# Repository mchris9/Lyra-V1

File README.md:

# Lyra-V1
Programmable Cross Over Network

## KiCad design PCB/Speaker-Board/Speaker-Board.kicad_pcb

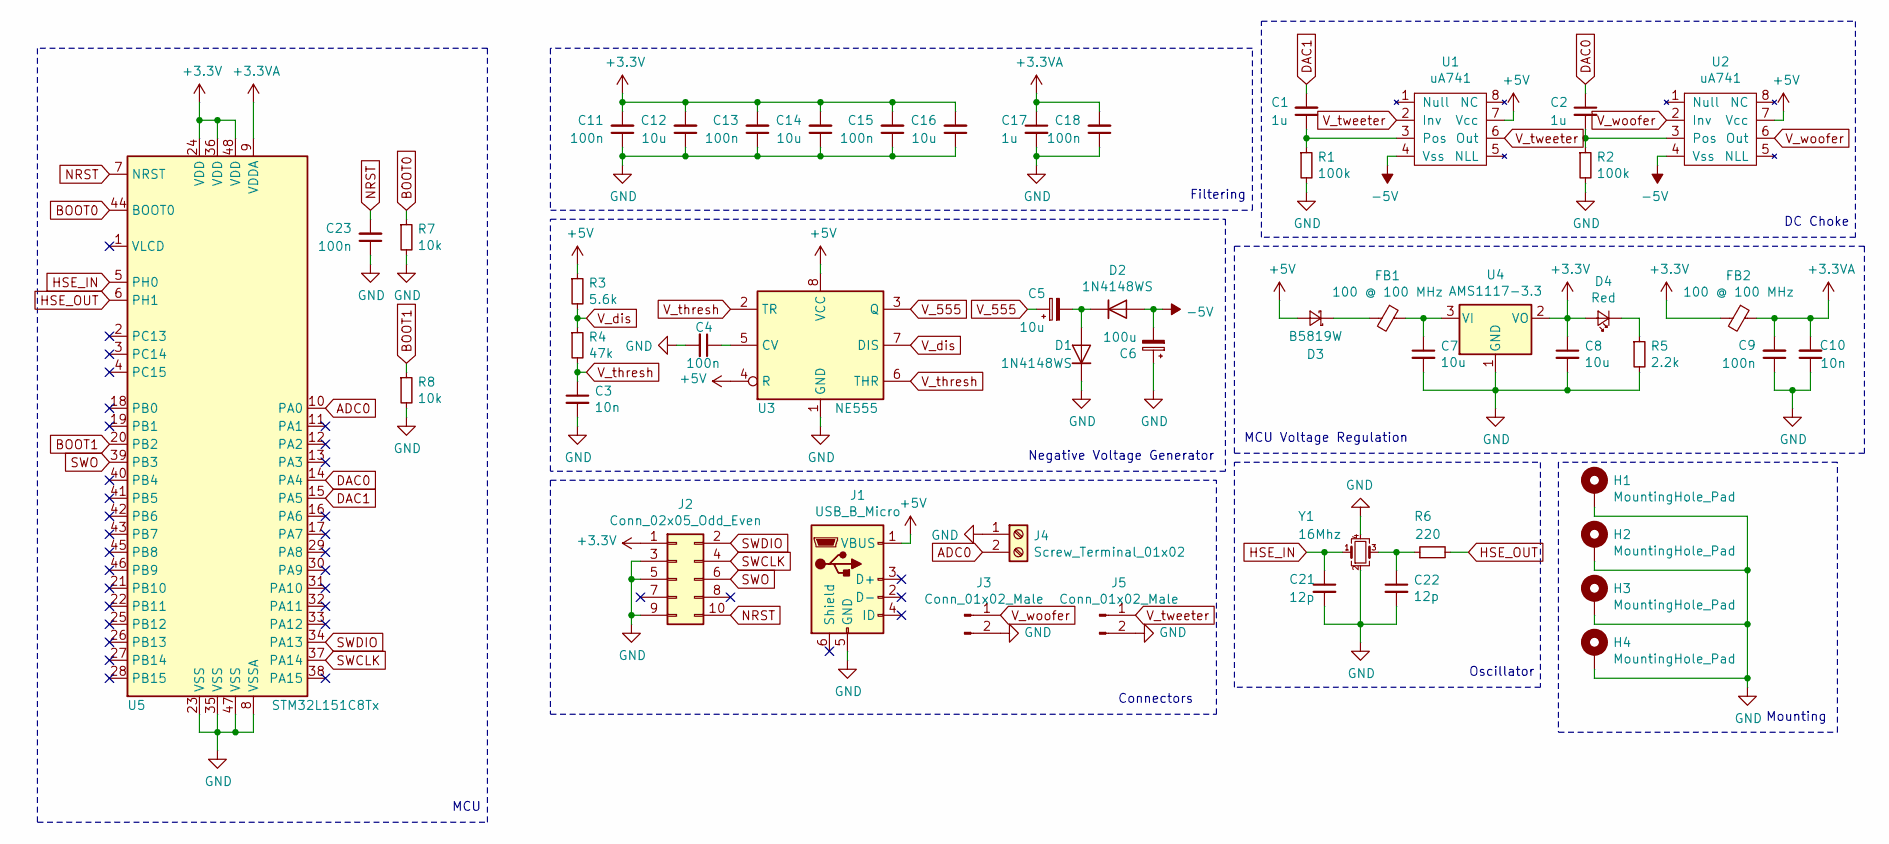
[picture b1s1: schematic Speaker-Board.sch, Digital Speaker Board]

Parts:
C1, C2, C17: 1u; C_0402_1005Metric; LCSC Part # C52923
C3: 10n; C_0402_1005Metric; LCSC Part # C15195
C4: 100n; C_0402_1005Metric; LCSC Part # C1525
C5: 10u; CP_Elec_4x5.3; LCSC Part # C134721
C6: 100u; CP_Elec_6.3x7.7; LCSC Part # C127971
C7, C8: 10u; C_0603_1608Metric; LCSC Part # C15195
C9: 100n; C_0603_1608Metric; LCSC Part # C14663
C10: 10n; C_0603_1608Metric; LCSC Part # C57112
C11, C13, C15, C18, C23: 100n; C_0402_1005Metric; LCSC Part # C14663
C12, C14, C16: 10u; C_0402_1005Metric; LCSC Part # C15195
C21, C22: 12p; C_0402_1005Metric; LCSC Part # C1547
D1, D2: 1N4148WS; D_SOD-323; LCSC Part # C2128
D3: B5819W; D_SOD-123; LCSC Part # C8598
D4: Red; LED_0603_1608Metric; LCSC Part # C2286
FB1, FB2: 100 @ 100 MHz; L_0805_2012Metric; LCSC Part # C1015
H1, H2, H3, H4: MountingHole_Pad; MountingHole_4.3mm_M4_Pad_Via
J1: USB_B_Micro; USB_Micro-B_Wuerth_629105150521; LCSC Part # C668589
J2: Conn_02x05_Odd_Even; PinHeader_2x05_P1.27mm_Vertical
J3, J5: Conn_01x02_Male; PinHeader_1x02_P1.27mm_Vertical
J4: Screw_Terminal_01x02; TerminalBlock_4Ucon_1x02_P3.50mm_Horizontal
R1, R2: 100k; R_0402_1005Metric; LCSC Part # C25086
R3: 5.6k; R_0402_1005Metric; LCSC Part # C25908
R4: 47k; R_0402_1005Metric; LCSC Part # C25792
R5: 2.2k; R_0603_1608Metric; LCSC Part # C4190
R6: 220; R_0402_1005Metric; LCSC Part # C25091
R7, R8: 10k; R_0402_1005Metric; LCSC Part # C25744
U1, U2: uA741; SOIC-8_3.9x4.9mm_P1.27mm; LCSC Part # C7111
U3: NE555; SOIC-8_3.9x4.9mm_P1.27mm; LCSC Part # C7593
U4: AMS1117-3.3; SOT-223-3_TabPin2; LCSC Part # C6186
U5: STM32L151C8Tx; LQFP-48_7x7mm_P0.5mm; LCSC Part # C9861
Y1: 16Mhz; Crystal_SMD_3225-4Pin_3.2x2.5mm; LCSC Part # C13738

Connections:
+3.3VA: C9.2, C10.2, C17.1, C18.2, FB2.1, U5.9 (VDDA)
+3V3: C8.1, C11.2, C12.2, C13.2, C14.2, C15.2, C16.2, D4.2 (A), FB2.2, J2.1, U4.2 (VO), U5.24 (VDD), U5.36 (VDD), U5.48 (VDD)
+5V: D3.2 (A), J1.1 (VBUS), R3.1, U1.7 (Vcc), U2.7 (Vcc), U3.4 (R), U3.8 (VCC)
-5V: C6.2, D2.2 (A), U1.4 (Vss), U2.4 (Vss)
ADC0: J4.2, U5.10 (PA0)
BOOT0: R7.1, U5.44 (BOOT0)
BOOT1: R8.1, U5.20 (PB2)
DAC0: C2.1, U5.14 (PA4)
DAC1: C1.2, U5.15 (PA5)
GND: C3.2, C4.2, C6.1, C7.2, C8.2, C9.1, C10.1, C11.1, C12.1, C13.1, C14.1, C15.1, C16.1, C17.2, C18.1, C21.2, C22.2, C23.1, D1.1 (K), H1.1, H2.1, H3.1, H4.1, J1.5 (GND), J2.3, J2.5, J2.9, J3.2, J4.1, J5.2, R1.2, R2.2, R5.2, R7.2, R8.2, U3.1 (GND), U4.1 (GND), U5.8 (VSSA), U5.23 (VSS), U5.35 (VSS), U5.47 (VSS), Y1.2, Y1.4
HSE_IN: C21.1, U5.5 (PH0), Y1.1
HSE_OUT: R6.2, U5.6 (PH1)
NRST: C23.2, J2.10, U5.7 (NRST)
unnamed: C1.1, R1.1, U1.3 (Pos)
unnamed: C2.2, R2.1, U2.3 (Pos)
unnamed: C4.1, U3.5 (CV)
unnamed: C5.2, D1.2 (A), D2.1 (K)
unnamed: C7.1, FB1.1, U4.3 (VI)
unnamed: C22.1, R6.1, Y1.3
unnamed: D3.1 (K), FB1.2
unnamed: D4.1 (K), R5.1
SWCLK: J2.4, U5.37 (PA14)
SWDIO: J2.2, U5.34 (PA13)
SWO: J2.6, U5.39 (PB3)
V_555: C5.1, U3.3 (Q)
V_dis: R3.2, R4.1, U3.7 (DIS)
V_thresh: C3.1, R4.2, U3.2 (TR), U3.6 (THR)
V_tweeter: J5.1, U1.2 (Inv), U1.6 (Out)
V_woofer: J3.1, U2.2 (Inv), U2.6 (Out)

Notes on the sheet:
Filtering
MCU Voltage Regulation
Negative Voltage Generator
DC Choke
Connectors
Oscillator
MCU
Mounting

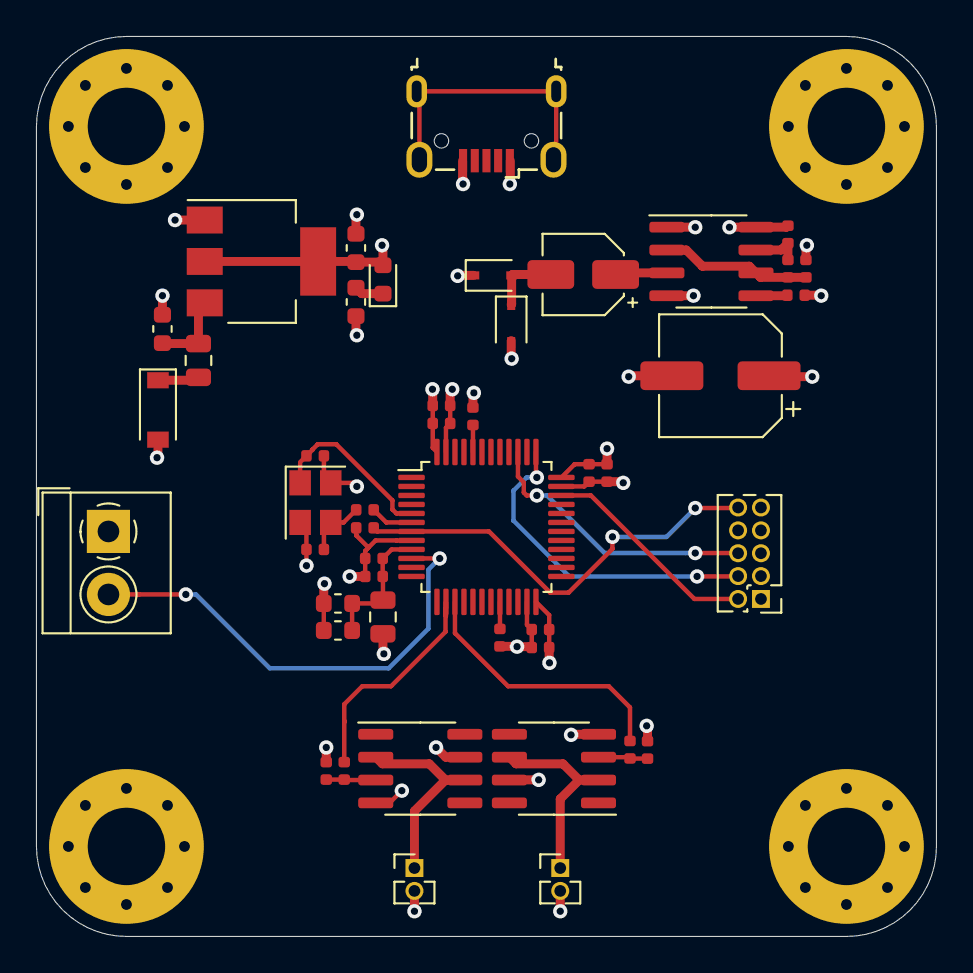
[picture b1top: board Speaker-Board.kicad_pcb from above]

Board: 6 copper layers, 50.0 x 50.0 mm, 50 parts (0 on the bottom side), 29 nets.

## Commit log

2021-09-21 Prior Work
2021-12-10 Updated Crossover
